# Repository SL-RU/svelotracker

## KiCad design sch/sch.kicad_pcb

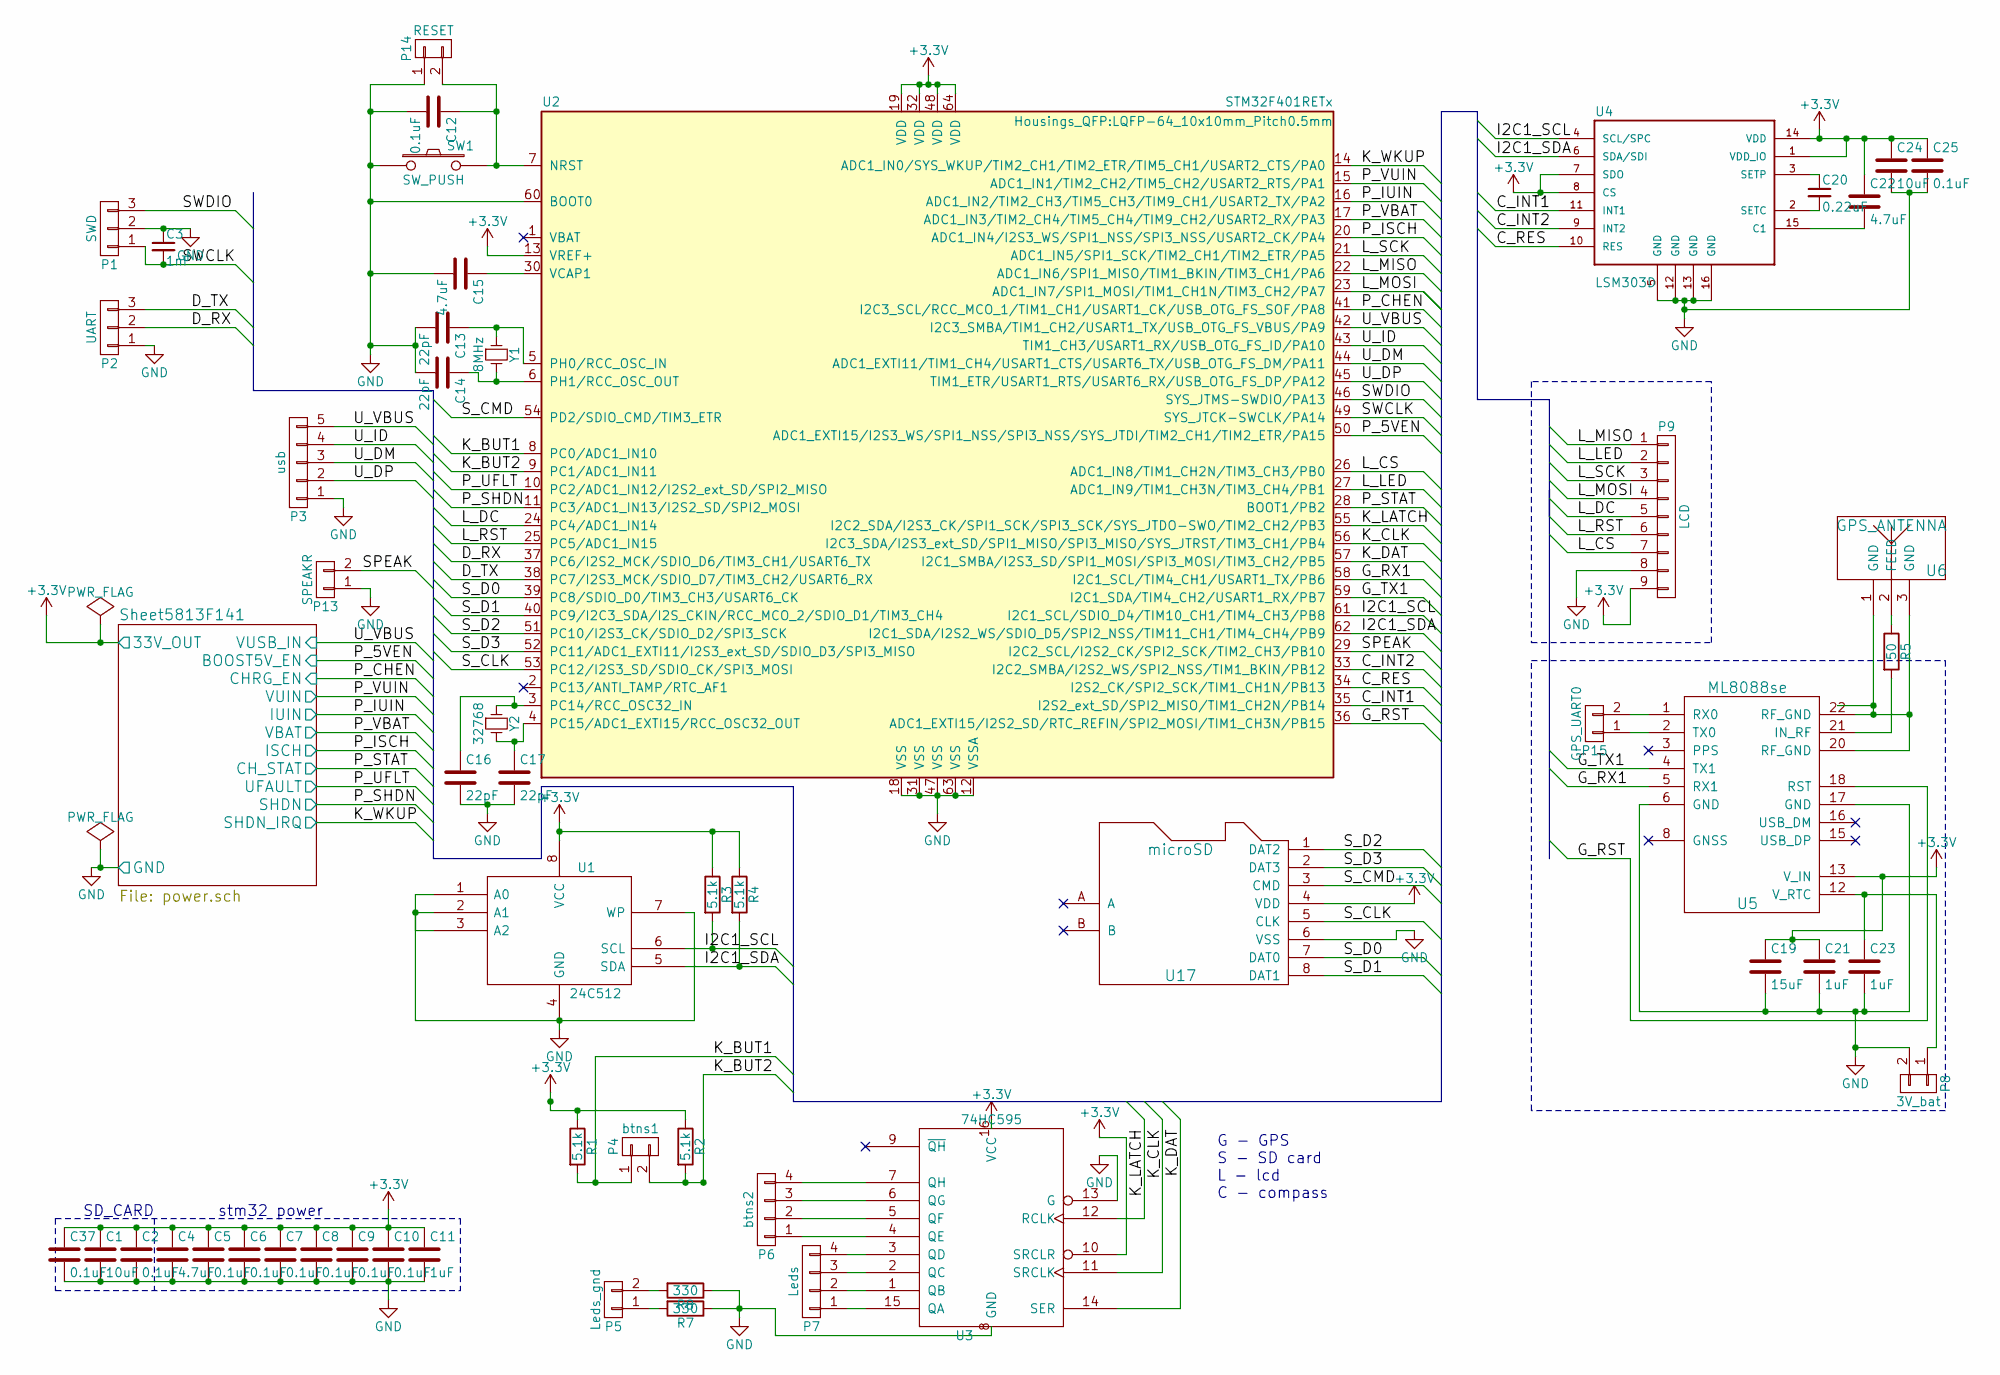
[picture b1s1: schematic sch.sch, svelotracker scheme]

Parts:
C1, C24: 10uF; C_0805
C2, C5, C6, C7, C8, C9, C10, C12, C25, C37: 0.1uF; C_0402
C3: 1nF; C_0402
C4, C15, C22: 4.7uF; C_0805
C11: 1uF; C_0805
C13, C14, C16, C17: 22pF; C_0805
C19: 15uF; C_0805
C20: 0.22uF; C_0805
C21, C23: 1uF; C_0402
P1: SWD; Pin_Header_Straight_1x03
P2: UART; Pin_Header_Straight_1x03
P3: usb; Pin_Header_Angled_1x05
P4: btns1; Pin_Header_Straight_1x02
P5: Leds_gnd; Pin_Header_Straight_1x02
P6: btns2; Pin_Header_Straight_1x04
P7: Leds; Pin_Header_Straight_1x04
P8: 3V_bat; Pin_Header_Straight_1x02
P9: LCD; Pin_Header_Straight_1x09
P13: SPEAKR; Pin_Header_Straight_1x02
P14: RESET; Pin_Header_Straight_1x02
P15: GPS_UART0; Pin_Header_Straight_1x02
R1, R2, R3, R4: 5.1k; R_0603
R5: 50; R_0603
R7, R8: 330; R_0603
SW1: SW_PUSH; SW_SPST_PTS645
U1: 24C512; SOIC-8-N
U2: STM32F401RETx; LQFP-64_10x10mm_Pitch0.5mm
U3: 74HC595; SOIC-16_3.9x9.9mm_Pitch1.27mm
U4: LSM303D; LGA-16-3x3
U5: ML8088se; ML8088sE
U6: GPS_ANTENNA; GSP_ANTENNA
U17: microSD; DM3D-SF
Y1: 8MHz; Crystal_SMD_5032_4Pads
Y2: 32768; Crystal_Round_Horizontal_2mm

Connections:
+3V3: C1.1, C2.1, C4.1, C5.1, C6.1, C7.1, C8.1, C9.1, C10.1, C11.1, C19.1, C21.1, C22.1, C24.1, C25.1, C37.1, P9.9, R1.1, R2.1, R3.1, R4.1, U1.8 (VCC), U2.13 (VREF+), U2.19 (VDD), U2.32 (VDD), U2.48 (VDD), U2.64 (VDD), U3.10 (SRCLR), U3.16 (VCC), U4.1 (VDD_IO), U4.7 (SDO), U4.8 (CS), U4.14 (VDD), U5.13 (V_IN), U17.4 (VDD); also elsewhere on the board
/C_INT1: U2.35 (I2S2_ext_SD/SPI2_MISO/TIM1_CH2N/PB14), U4.11 (INT1)
/C_INT2: U2.33 (I2C2_SMBA/I2S2_WS/SPI2_NSS/TIM1_BKIN/PB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), U4.9 (INT2)
/C_RES: U2.34 (I2S2_CK/SPI2_SCK/TIM1_CH1N/PB13), U4.10 (RES)
/D_RX: P2.2, U2.37 (PC6/I2S2_MCK/SDIO_D6/TIM3_CH1/USART6_TX)
/D_TX: P2.3, U2.38 (PC7/I2S3_MCK/SDIO_D7/TIM3_CH2/USART6_RX)
/G_RST: U2.36 (ADC1_EXTI15/I2S2_SD/RTC_REFIN/SPI2_MOSI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), U5.18 (RST)
/G_RX1: U2.58 (I2C1_SCL/TIM4_CH1/USART1_TX/PB6), U5.5 (RX1)
/G_TX1: U2.59 (I2C1_SDA/TIM4_CH2/USART1_RX/PB7), U5.4 (TX1)
/I2C1_SCL: R3.2, U1.6 (SCL), U2.61 (I2C1_SCL/SDIO_D4/TIM10_CH1/TIM4_CH3/PB8), U4.4 (SCL/SPC)
/I2C1_SDA: R4.2, U1.5 (SDA), U2.62 (I2C1_SDA/I2S2_WS/SDIO_D5/SPI2_NSS/TIM11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), U4.6 (SDA/SDI)
/K_BUT1: P4.1, R1.2, U2.8 (PC0/ADC1_IN10)
/K_BUT2: P4.2, R2.2, U2.9 (PC1/ADC1_IN11)
/K_CLK: U2.56 (I2C3_SDA/I2S3_ext_SD/SPI1_MISO/SPI3_MIS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), U3.11 (SRCLK)
/K_DAT: U2.57 (I2C1_SMBA/I2S3_SD/SPI1_MOSI/SPI3_MOSI/T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), U3.14 (SER)
/K_LATCH: U2.55 (I2C2_SDA/I2S3_CK/SPI1_SCK/SPI3_SCK/SYS_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), U3.12 (RCLK)
/L_CS: P9.7, U2.26 (ADC1_IN8/TIM1_CH2N/TIM3_CH3/PB0)
/L_DC: P9.5, U2.24 (PC4/ADC1_IN14)
/L_LED: P9.2, U2.27 (ADC1_IN9/TIM1_CH3N/TIM3_CH4/PB1)
/L_MISO: P9.1, U2.22 (ADC1_IN6/SPI1_MISO/TIM1_BKIN/TIM3_CH1/P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)
/L_MOSI: P9.4, U2.23 (ADC1_IN7/SPI1_MOSI/TIM1_CH1N/TIM3_CH2/P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)
/L_RST: P9.6, U2.25 (PC5/ADC1_IN15)
/L_SCK: P9.3, U2.21 (ADC1_IN5/SPI1_SCK/TIM2_CH1/TIM2_ETR/PA5)
/SPEAK: P13.2, U2.29 (I2C2_SCL/I2S2_CK/SPI2_SCK/TIM2_CH3/PB10)
/SWCLK: C3.2, P1.1, U2.49 (SYS_JTCK-SWCLK/PA14)
/SWDIO: P1.3, U2.46 (SYS_JTMS-SWDIO/PA13)
/S_CLK: U2.53 (PC12/I2S3_SD/SDIO_CK/SPI3_MOSI), U17.5 (CLK)
/S_CMD: U2.54 (PD2/SDIO_CMD/TIM3_ETR), U17.3 (CMD)
/S_D0: U2.39 (PC8/SDIO_D0/TIM3_CH3/USART6_CK), U17.7 (DAT0)
/S_D1: U2.40 (PC9/I2C3_SDA/I2S_CKIN/RCC_MCO_2/SDIO_D1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), U17.8 (DAT1)
/S_D2: U2.51 (PC10/I2S3_CK/SDIO_D2/SPI3_SCK), U17.1 (DAT2)
/S_D3: U2.52 (PC11/ADC1_EXTI11/I2S3_ext_SD/SDIO_D3/SP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), U17.2 (DAT3)
/Sheet5813F141/BOOST5V_EN: U2.50 (ADC1_EXTI15/I2S3_WS/SPI1_NSS/SPI3_NSS/S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); also elsewhere on the board
/Sheet5813F141/CHRG_EN: U2.41 (I2C3_SCL/RCC_MCO_1/TIM1_CH1/USART1_CK/U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); also elsewhere on the board
/Sheet5813F141/CH_STAT: U2.28 (BOOT1/PB2); also elsewhere on the board
/Sheet5813F141/ISCH: U2.20 (ADC1_IN4/I2S3_WS/SPI1_NSS/SPI3_NSS/USAR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); also elsewhere on the board
/Sheet5813F141/IUIN: U2.16 (ADC1_IN2/TIM2_CH3/TIM5_CH3/TIM9_CH1/USA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); also elsewhere on the board
/Sheet5813F141/SHDN: U2.11 (PC3/ADC1_IN13/I2S2_SD/SPI2_MOSI); also elsewhere on the board
/Sheet5813F141/SHDN_IRQ: U2.14 (ADC1_IN0/SYS_WKUP/TIM2_CH1/TIM2_ETR/TIM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); also elsewhere on the board
/Sheet5813F141/UFAULT: U2.10 (PC2/ADC1_IN12/I2S2_ext_SD/SPI2_MISO); also elsewhere on the board
/Sheet5813F141/VBAT: U2.17 (ADC1_IN3/TIM2_CH4/TIM5_CH4/TIM9_CH2/USA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); also elsewhere on the board
/Sheet5813F141/VUIN: U2.15 (ADC1_IN1/TIM2_CH2/TIM5_CH2/USART2_RTS/P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); also elsewhere on the board
/Sheet5813F141/VUSB_IN: P3.5, U2.42 (I2C3_SMBA/TIM1_CH2/USART1_TX/USB_OTG_FS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); also elsewhere on the board
/U_DM: P3.3, U2.44 (ADC1_EXTI11/TIM1_CH4/USART1_CTS/USART6_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)
/U_DP: P3.2, U2.45 (TIM1_ETR/USART1_RTS/USART6_RX/USB_OTG_F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)
/U_ID: P3.4, U2.43 (TIM1_CH3/USART1_RX/USB_OTG_FS_ID/PA10)
GND: C1.2, C2.2, C3.1, C4.2, C5.2, C6.2, C7.2, C8.2, C9.2, C10.2, C11.2, C12.2, C13.2, C14.2, C15.2, C16.2, C17.2, C19.2, C21.2, C23.2, C24.2, C25.2, C37.2, P1.2, P2.1, P3.1, P8.2, P9.8, P13.1, P14.1, R7.1, R8.1, SW1.1, U1.1 (A0), U1.2 (A1), U1.3 (A2), U1.4 (GND), U1.7 (WP), U2.12 (VSSA), U2.18 (VSS), U2.31 (VSS), U2.47 (VSS), U2.60 (BOOT0), U2.63 (VSS), U3.8 (GND), U3.13 (G), U4.5 (GND), U4.12 (GND), U4.13 (GND), U4.16 (GND), U5.6 (GND), U5.17 (GND), U17.6 (VSS); also elsewhere on the board
unnamed: C12.1, P14.2, SW1.2, U2.7 (NRST)
unnamed: C13.1, U2.5 (PH0/RCC_OSC_IN), Y1.1
unnamed: C14.1, U2.6 (PH1/RCC_OSC_OUT), Y1.2
unnamed: C15.1, U2.30 (VCAP1)
unnamed: C16.1, U2.3 (PC14/RCC_OSC32_IN), Y2.1
unnamed: C17.1, U2.4 (PC15/ADC1_EXTI15/RCC_OSC32_OUT), Y2.2
unnamed: C20.1, U4.3 (SETP)
unnamed: C20.2, U4.2 (SETC)
unnamed: C22.2, U4.15 (C1)
unnamed: C23.1, P8.1, U5.12 (V_RTC)
unnamed: P5.1, R7.2
unnamed: P5.2, R8.2
unnamed: P6.1, U3.4 (QE)
unnamed: P6.2, U3.5 (QF)
unnamed: P6.3, U3.6 (QG)
unnamed: P6.4, U3.7 (QH)
unnamed: P7.1, U3.15 (QA)
unnamed: P7.2, U3.1 (QB)
unnamed: P7.3, U3.2 (QC)
unnamed: P7.4, U3.3 (QD)
unnamed: P15.1, U5.2 (TX0)
unnamed: P15.2, U5.1 (RX0)
unnamed: R5.1, U6.2 (FEED)
unnamed: R5.2, U5.21 (IN_RF)
unnamed: U5.20 (RF_GND), U5.22 (RF_GND), U6.1 (GND), U6.3 (GND)

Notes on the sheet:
G - GPS S - SD card L - lcd C - compass
stm32 power
SD_CARD

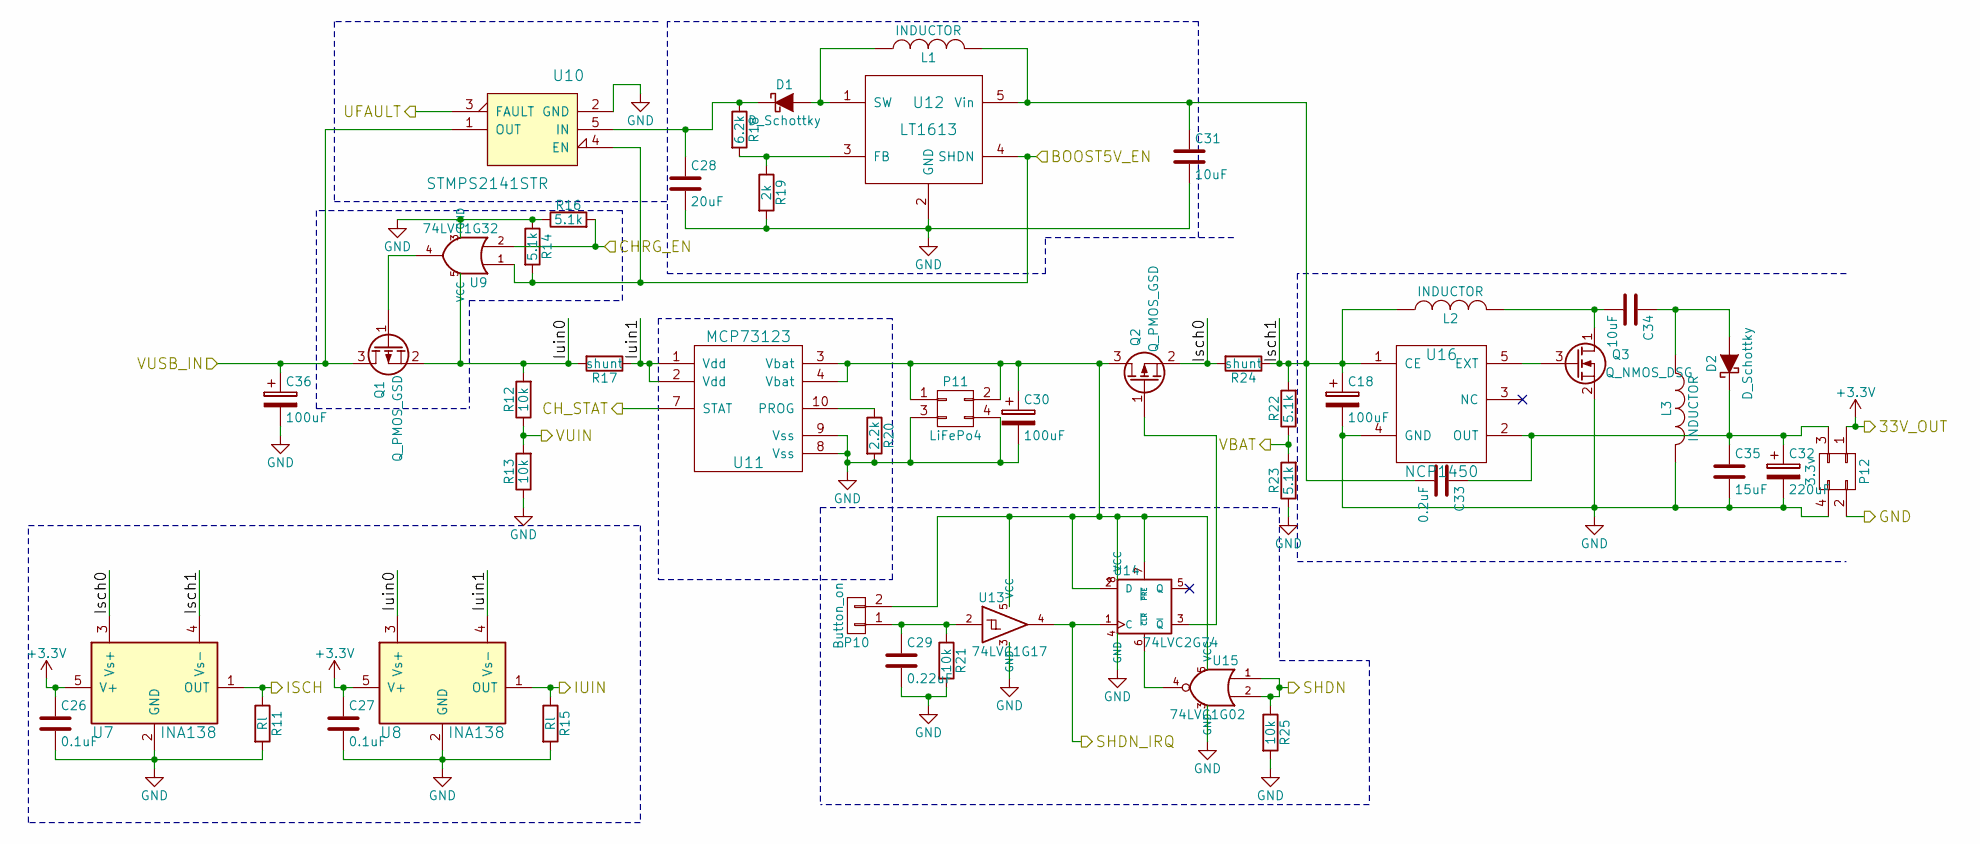
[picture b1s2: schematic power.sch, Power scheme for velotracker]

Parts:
C18, C30, C36: 100uF; C_Radial_D5_L11_P2.5
C26, C27: 0.1uF; C_0402
C28: 20uF; C_0805
C29: 0.22uF; C_0805
C31, C34: 10uF; C_0805
C32: 220uF; C_Radial_D5_L11_P2.5
C33: 0.2uF; C_0805
C35: 15uF; C_0805
D1, D2: D_Schottky; DO-214AC(SMA)
L1, L2, L3: INDUCTOR; Choke_SMD_Wuerth-WE-PD2-Typ-L
P10: Button_on; Pin_Header_Straight_1x02
P11: LiFePo4; Pin_Header_Straight_2x02
P12: 3.3v; Pin_Header_Straight_2x02
Q1, Q2: Q_PMOS_GSD; SOT-23
Q3: Q_NMOS_DSG; SOT-23
R11, R15: Rl; R_0603
R12, R13, R21, R25: 10k; R_0603
R14, R16, R22, R23: 5.1k; R_0603
R17, R24: shunt; R_2010
R18: 6.2k; R_0603
R19: 2k; R_0805
R20: 2.2k; R_0603
U7, U8: INA138; SOT-23-5
U9: 74LVC1G32; SOT-353
U10: STMPS2141STR; SOT-23-5
U11: MCP73123; DFN-10-1EP_3x3mm_Pitch0.5mm
U12: LT1613; SOT-23-5
U13: 74LVC1G17; SOT-353
U14: 74LVC2G74; SSOP8
U15: 74LVC1G02; SOT-23-5
U16: NCP1450; SOT-23-5

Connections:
+3V3: C26.1, C27.1, P12.1, U7.5 (V+), U8.5 (V+); also elsewhere on the board
/Sheet5813F141/BOOST5V_EN: R14.2, U9.1, U10.4 (EN), U12.4 (SHDN); also elsewhere on the board
/Sheet5813F141/CHRG_EN: R16.2, U9.2; also elsewhere on the board
/Sheet5813F141/CH_STAT: U11.7 (STAT); also elsewhere on the board
/Sheet5813F141/ISCH: R11.1, U7.1 (OUT); also elsewhere on the board
/Sheet5813F141/IUIN: R15.1, U8.1 (OUT); also elsewhere on the board
/Sheet5813F141/Isch0: Q2.2 (S), R24.2, U7.3 (Vs+)
/Sheet5813F141/Isch1: C18.1, C31.1, C33.2, L1.2, L2.1, R22.2, R24.1, U7.4 (Vs-), U12.5 (Vin), U16.1 (CE)
/Sheet5813F141/Iuin0: Q1.2 (S), R12.2, R17.2, U8.3 (Vs+), U9.5 (VCC)
/Sheet5813F141/Iuin1: R17.1, U8.4 (Vs-), U11.1 (Vdd), U11.2 (Vdd)
/Sheet5813F141/SHDN: R25.1, U15.1, U15.2; also elsewhere on the board
/Sheet5813F141/SHDN_IRQ: U13.4, U14.1 (C); also elsewhere on the board
/Sheet5813F141/UFAULT: U10.3 (FAULT); also elsewhere on the board
/Sheet5813F141/VBAT: R22.1, R23.2; also elsewhere on the board
/Sheet5813F141/VUIN: R12.1, R13.2; also elsewhere on the board
/Sheet5813F141/VUSB_IN: C36.1, Q1.3 (D), U10.1 (OUT); also elsewhere on the board
GND: C18.2, C26.2, C27.2, C28.2, C29.2, C30.2, C31.2, C32.2, C35.2, C36.2, L3.2, P11.3, P11.4, P12.2, P12.4, Q3.2 (S), R11.2, R13.1, R14.1, R15.2, R16.1, R19.2, R20.2, R21.2, R23.1, R25.2, U7.2 (GND), U8.2 (GND), U9.3 (GND), U10.2 (GND), U11.8 (Vss), U11.9 (Vss), U12.2 (GND), U13.3 (GND), U14.4 (GND), U15.3 (GND), U16.4 (GND); also elsewhere on the board
unnamed: C28.1, D1.1 (K), R18.1, U10.5 (IN)
unnamed: C29.1, P10.1, R21.1, U13.2
unnamed: C30.1, P10.2, P11.1, P11.2, Q2.3 (D), U11.3 (Vbat), U11.4 (Vbat), U13.5 (VCC), U14.2 (D), U14.7 (~PRE), U14.8 (VCC), U15.5 (VCC)
unnamed: C32.1, C33.1, C35.1, D2.1 (K), P12.3, U16.2 (OUT)
unnamed: C34.1, D2.2 (A), L3.1
unnamed: C34.2, L2.2, Q3.1 (D)
unnamed: D1.2 (A), L1.1, U12.1 (SW)
unnamed: Q1.1 (G), U9.4
unnamed: Q2.1 (G), U14.3 (~Q)
unnamed: Q3.3 (G), U16.5 (EXT)
unnamed: R18.2, R19.1, U12.3 (FB)
unnamed: R20.1, U11.10 (PROG)
unnamed: U14.6 (~CLR), U15.4

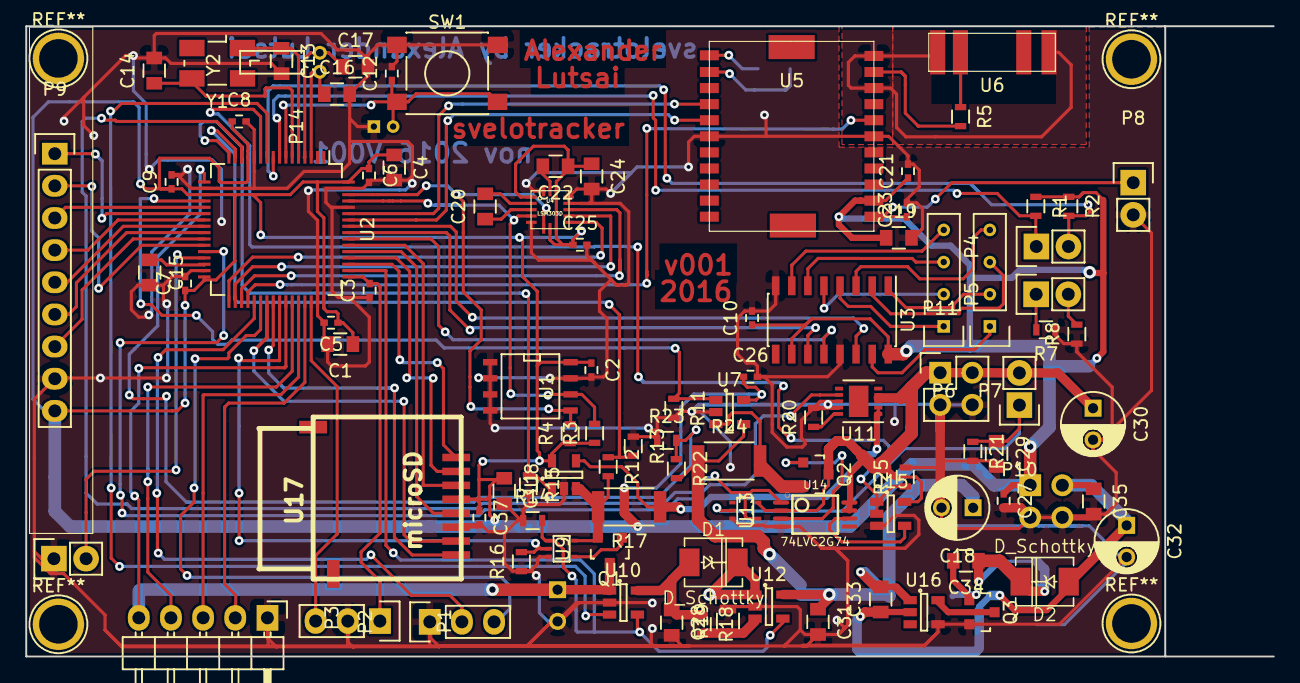
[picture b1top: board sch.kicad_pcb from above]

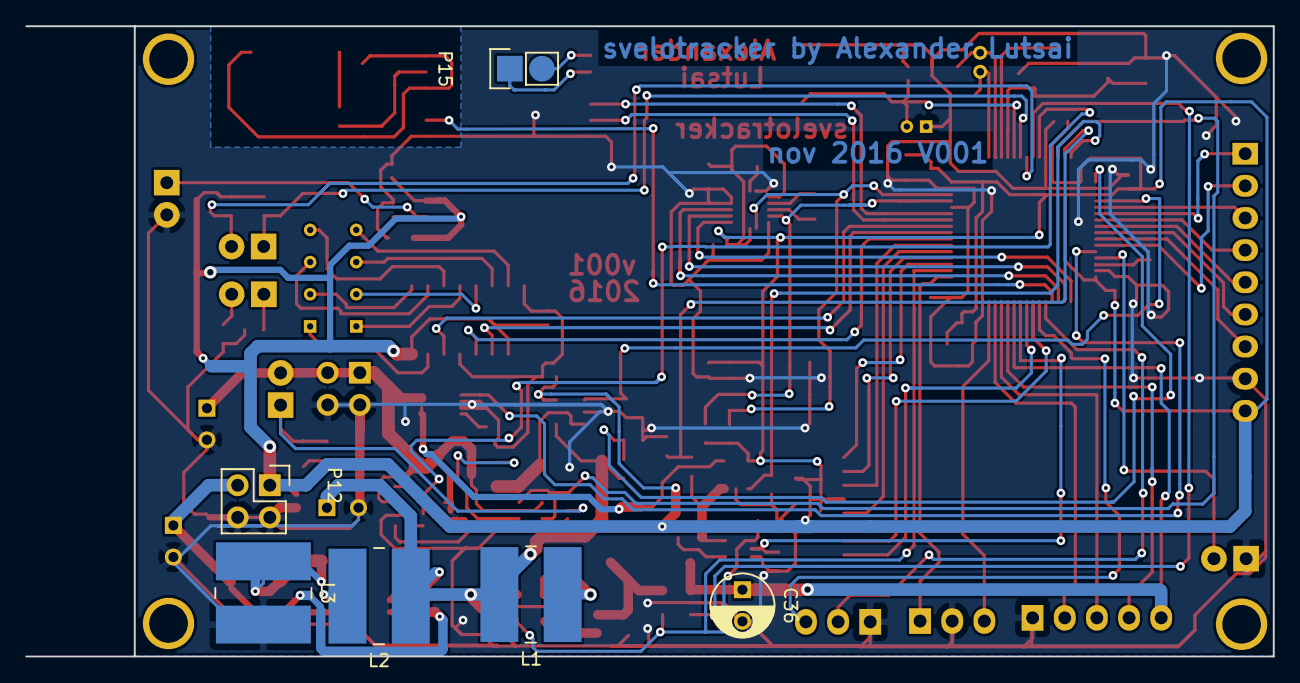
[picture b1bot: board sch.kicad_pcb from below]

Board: 2 copper layers, 98.6 x 49.8 mm, 102 parts (6 on the bottom side), 89 nets.

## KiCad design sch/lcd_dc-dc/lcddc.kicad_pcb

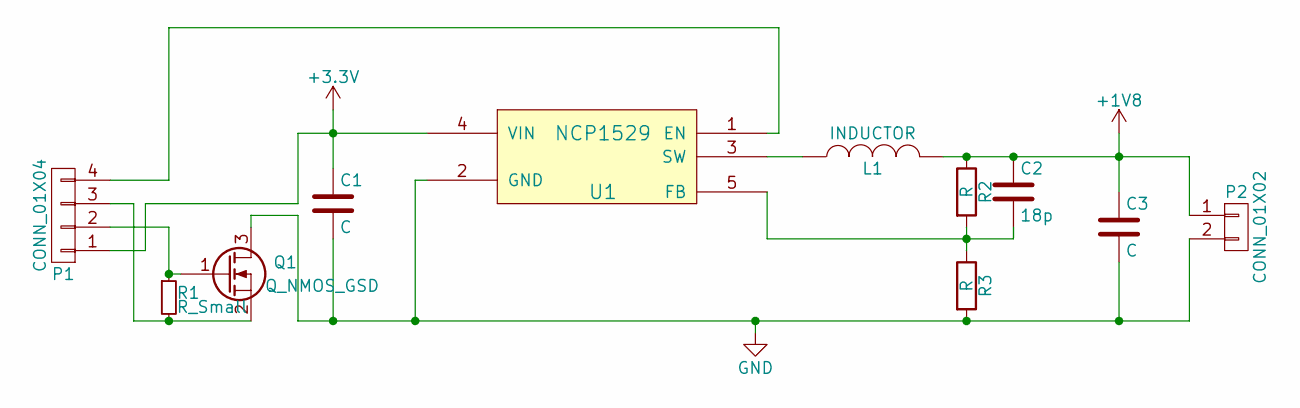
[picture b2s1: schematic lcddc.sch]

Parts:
C1, C3: C; C_0805_HandSoldering
C2: 18p; C_0805_HandSoldering
L1: INDUCTOR; CDRH2D14
P1: CONN_01X04; Pin_Header_Straight_1x04
P2: CONN_01X02; Pin_Header_Straight_1x02
Q1: Q_NMOS_GSD; SOT-23
R1: R_Small; R_0603_HandSoldering
R2, R3: R; R_0603_HandSoldering
U1: NCP1529; SOT-23-5

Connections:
+1V8: C2.1, C3.1, L1.2, P2.1, R2.1
+3V3: C1.1, P1.1, U1.4 (VIN)
GND: C1.2, C3.2, P2.2, Q1.3 (D), R3.2, U1.2 (GND)
unnamed: C2.2, R2.2, R3.1, U1.5 (FB)
unnamed: L1.1, U1.3 (SW)
unnamed: P1.2, Q1.1 (G), R1.1
unnamed: P1.3, Q1.2 (S), R1.2
unnamed: P1.4, U1.1 (EN)

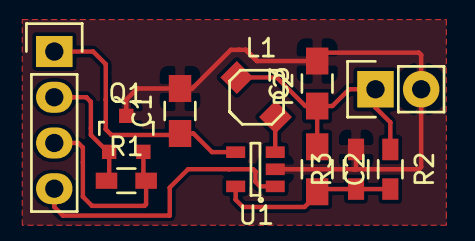
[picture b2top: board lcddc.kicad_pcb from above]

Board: 2 copper layers, 11 parts (0 on the bottom side), 8 nets.

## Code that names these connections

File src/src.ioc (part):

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Mcu.Name=STM32F401R(D-E)Tx
Mcu.Package=LQFP64
Mcu.UserName=STM32F401RETx
PA0-WKUP.GPIOParameters=GPIO_Label
PA0-WKUP.GPIO_Label=K_WKUP
PA0-WKUP.Mode=SYS_WakeUp0
PA0-WKUP.Signal=SYS_WKUP
PA1.GPIOParameters=GPIO_Label
PA1.GPIO_Label=P_VUIN
PA1.Signal=ADCx_IN1
PA10.Mode=OTG/Dual_Role_Device
PA10.Signal=USB_OTG_FS_ID
PA11.Mode=OTG/Dual_Role_Device
PA11.Signal=USB_OTG_FS_DM
PA12.Mode=OTG/Dual_Role_Device
PA12.Signal=USB_OTG_FS_DP
PA13.Mode=Serial_Wire
PA13.Signal=SYS_JTMS-SWDIO
PA14.Mode=Serial_Wire
PA14.Signal=SYS_JTCK-SWCLK
PA15.GPIOParameters=GPIO_Label
PA15.GPIO_Label=BOOST5V_EN
PA15.Signal=GPIO_Output
PA2.GPIOParameters=GPIO_Label
PA2.GPIO_Label=P_IUIN
PA2.Signal=ADCx_IN2
PA3.GPIOParameters=GPIO_Label
PA3.GPIO_Label=P_VBAT
PA3.Signal=ADCx_IN3
PA4.GPIOParameters=GPIO_Label
PA4.GPIO_Label=P_ISCH
PA4.Signal=ADCx_IN4
PA5.Mode=Full_Duplex_Master
PA5.Signal=SPI1_SCK
PA6.Mode=Full_Duplex_Master
PA6.Signal=SPI1_MISO
PA7.Mode=Full_Duplex_Master
PA7.Signal=SPI1_MOSI
PA8.GPIOParameters=GPIO_Label
PA8.GPIO_Label=CHRG_EN
PA8.Signal=GPIO_Output
PA9.Mode=Activate_VBUS
PA9.Signal=USB_OTG_FS_VBUS
PB0.GPIOParameters=GPIO_Label
PB0.GPIO_Label=L_CS
PB0.Signal=GPIO_Output
PB1.GPIOParameters=GPIO_Label
PB1.GPIO_Label=L_LED
PB1.Signal=GPIO_Output
PB12.GPIOParameters=GPIO_Label
PB12.GPIO_Label=C_INT2
PB12.Signal=GPXTI12
PB13.GPIOParameters=GPIO_Label
PB13.GPIO_Label=C_RES
PB13.Signal=GPIO_Output
PB14.GPIOParameters=GPIO_Label
PB14.GPIO_Label=C_INT1
PB14.Signal=GPXTI14
PB15.GPIOParameters=GPIO_Label
PB15.GPIO_Label=G_RST
PB15.Signal=GPIO_Output
PB2.GPIOParameters=GPIO_Label
PB2.GPIO_Label=P_STAT
PB2.Signal=GPIO_Input
PB3.GPIOParameters=GPIO_Label
PB3.GPIO_Label=K_LATCH
PB3.Signal=GPIO_Output
PB4.GPIOParameters=GPIO_Label
PB4.GPIO_Label=K_CLK
PB4.Signal=GPIO_Output
PB5.GPIOParameters=GPIO_Label
PB5.GPIO_Label=K_DAT
PB5.Signal=GPIO_Output
PB6.Mode=Asynchronous
PB6.Signal=USART1_TX
PB7.Mode=Asynchronous
PB7.Signal=USART1_RX
PB8.Mode=I2C
PB8.Signal=I2C1_SCL
PB9.Mode=I2C
PB9.Signal=I2C1_SDA
PC0.GPIOParameters=GPIO_Label
PC0.GPIO_Label=K_BUT1
PC0.Signal=GPIO_Input
PC1.GPIOParameters=GPIO_Label
PC1.GPIO_Label=K_BUT2
PC1.Signal=GPIO_Input
PC10.Mode=SD_4_bits_Wide_bus
PC10.Signal=SDIO_D2
PC11.Mode=SD_4_bits_Wide_bus
PC11.Signal=SDIO_D3
PC12.Mode=SD_4_bits_Wide_bus
PC12.Signal=SDIO_CK
PC14-OSC32_IN.Mode=LSE-External-Oscillator
PC14-OSC32_IN.Signal=RCC_OSC32_IN
PC15-OSC32_OUT.Mode=LSE-External-Oscillator
PC15-OSC32_OUT.Signal=RCC_OSC32_OUT
PC2.GPIOParameters=GPIO_Label
PC2.GPIO_Label=P_UFLT
PC2.Signal=GPIO_Input
PC3.GPIOParameters=GPIO_Label
PC3.GPIO_Label=P_SHDN
PC3.Signal=GPIO_Output
PC4.GPIOParameters=GPIO_Label
PC4.GPIO_Label=L_DC
PC4.Signal=GPIO_Output
PC5.GPIOParameters=GPIO_Label
PC5.GPIO_Label=L_RST
PC5.Signal=GPIO_Output
PC6.Mode=Asynchronous
PC6.Signal=USART6_TX
PC7.Mode=Asynchronous
PC7.Signal=USART6_RX
PC8.Mode=SD_4_bits_Wide_bus
PC8.Signal=SDIO_D0
PC9.Mode=SD_4_bits_Wide_bus
PC9.Signal=SDIO_D1
PD2.Mode=SD_4_bits_Wide_bus
PD2.Signal=SDIO_CMD
PH0\ -\ OSC_IN.Mode=HSE-External-Oscillator
PH0\ -\ OSC_IN.Signal=RCC_OSC_IN
PH1\ -\ OSC_OUT.Mode=HSE-External-Oscillator
PH1\ -\ OSC_OUT.Signal=RCC_OSC_OUT
RCC.HSE_VALUE=8000000
RCC.SYSCLKFreq_VALUE=84000000
RCC.SYSCLKSource=RCC_SYSCLKSOURCE_PLLCLK
board=src

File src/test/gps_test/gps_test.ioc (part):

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Mcu.Name=STM32F401R(D-E)Tx
Mcu.Package=LQFP64
Mcu.UserName=STM32F401RETx
PA0-WKUP.Mode=SYS_WakeUp0
PA0-WKUP.Signal=SYS_WKUP
PA13.Mode=Serial_Wire
PA13.Signal=SYS_JTMS-SWDIO
PA14.Mode=Serial_Wire
PA14.Signal=SYS_JTCK-SWCLK
PA5.Mode=Full_Duplex_Master
PA5.Signal=SPI1_SCK
PA6.Mode=Full_Duplex_Master
PA6.Signal=SPI1_MISO
PA7.Mode=Full_Duplex_Master
PA7.Signal=SPI1_MOSI
PB0.GPIOParameters=GPIO_Label
PB0.GPIO_Label=l_cs
PB0.Signal=GPIO_Output
PB1.Signal=S_TIM3_CH4
PB10.Signal=GPIO_Output
PB12.Signal=GPXTI12
PB14.Signal=GPXTI14
PB15.GPIOParameters=GPIO_Label
PB15.GPIO_Label=G_RST
PB15.Signal=GPIO_Output
PB3.GPIOParameters=GPIO_Label
PB3.GPIO_Label=k_latch
PB3.Signal=GPIO_Output
PB4.GPIOParameters=GPIO_Label
PB4.GPIO_Label=k_clk
PB4.Signal=GPIO_Output
PB5.GPIOParameters=GPIO_Label
PB5.GPIO_Label=k_DAT
PB5.Signal=GPIO_Output
PB6.GPIOParameters=GPIO_Label
PB6.GPIO_Label=G_RX1
PB6.Mode=Asynchronous
PB6.Signal=USART1_TX
PB7.GPIOParameters=GPIO_Label
PB7.GPIO_Label=G_TX1
PB7.Mode=Asynchronous
PB7.Signal=USART1_RX
PB8.Mode=I2C
PB8.Signal=I2C1_SCL
PB9.Mode=I2C
PB9.Signal=I2C1_SDA
PC0.Signal=GPIO_Input
PC1.Signal=GPIO_Input
PC10.Mode=SD_4_bits_Wide_bus
PC10.Signal=SDIO_D2
PC11.Mode=SD_4_bits_Wide_bus
PC11.Signal=SDIO_D3
PC12.Mode=SD_4_bits_Wide_bus
PC12.Signal=SDIO_CK
PC4.GPIOParameters=GPIO_Label
PC4.GPIO_Label=l_dc
PC4.Signal=GPIO_Output
PC5.GPIOParameters=GPIO_Label
PC5.GPIO_Label=l_rst
PC5.Signal=GPIO_Output
PC6.Mode=Asynchronous
PC6.Signal=USART6_TX
PC7.Mode=Asynchronous
PC7.Signal=USART6_RX
PC8.Mode=SD_4_bits_Wide_bus
PC8.Signal=SDIO_D0
PC9.Mode=SD_4_bits_Wide_bus
PC9.Signal=SDIO_D1
PD2.Mode=SD_4_bits_Wide_bus
PD2.Signal=SDIO_CMD
PH0\ -\ OSC_IN.Mode=HSE-External-Oscillator
PH0\ -\ OSC_IN.Signal=RCC_OSC_IN
PH1\ -\ OSC_OUT.Mode=HSE-External-Oscillator
PH1\ -\ OSC_OUT.Signal=RCC_OSC_OUT
RCC.HSE_VALUE=8000000
RCC.SYSCLKFreq_VALUE=84000000
RCC.SYSCLKSource=RCC_SYSCLKSOURCE_PLLCLK
board=gps_test

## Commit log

2016-10-30 power done
2016-10-31 footprints done
2016-11-02 layout 60%
2016-11-03 pcb 100%
2016-11-03 name on pcb
2016-11-08 pcb ready. gerber files also.
2016-11-15 to rezonit
2016-11-23 sd card 180 degree rotation
2016-11-29 via size for rezonit
2016-12-09 lcd dc converter fix
2017-02-20 added gps test project
2017-02-20 I2C test
2017-02-22 temp
2017-02-27 accelerometer
2017-02-28 git submodules
